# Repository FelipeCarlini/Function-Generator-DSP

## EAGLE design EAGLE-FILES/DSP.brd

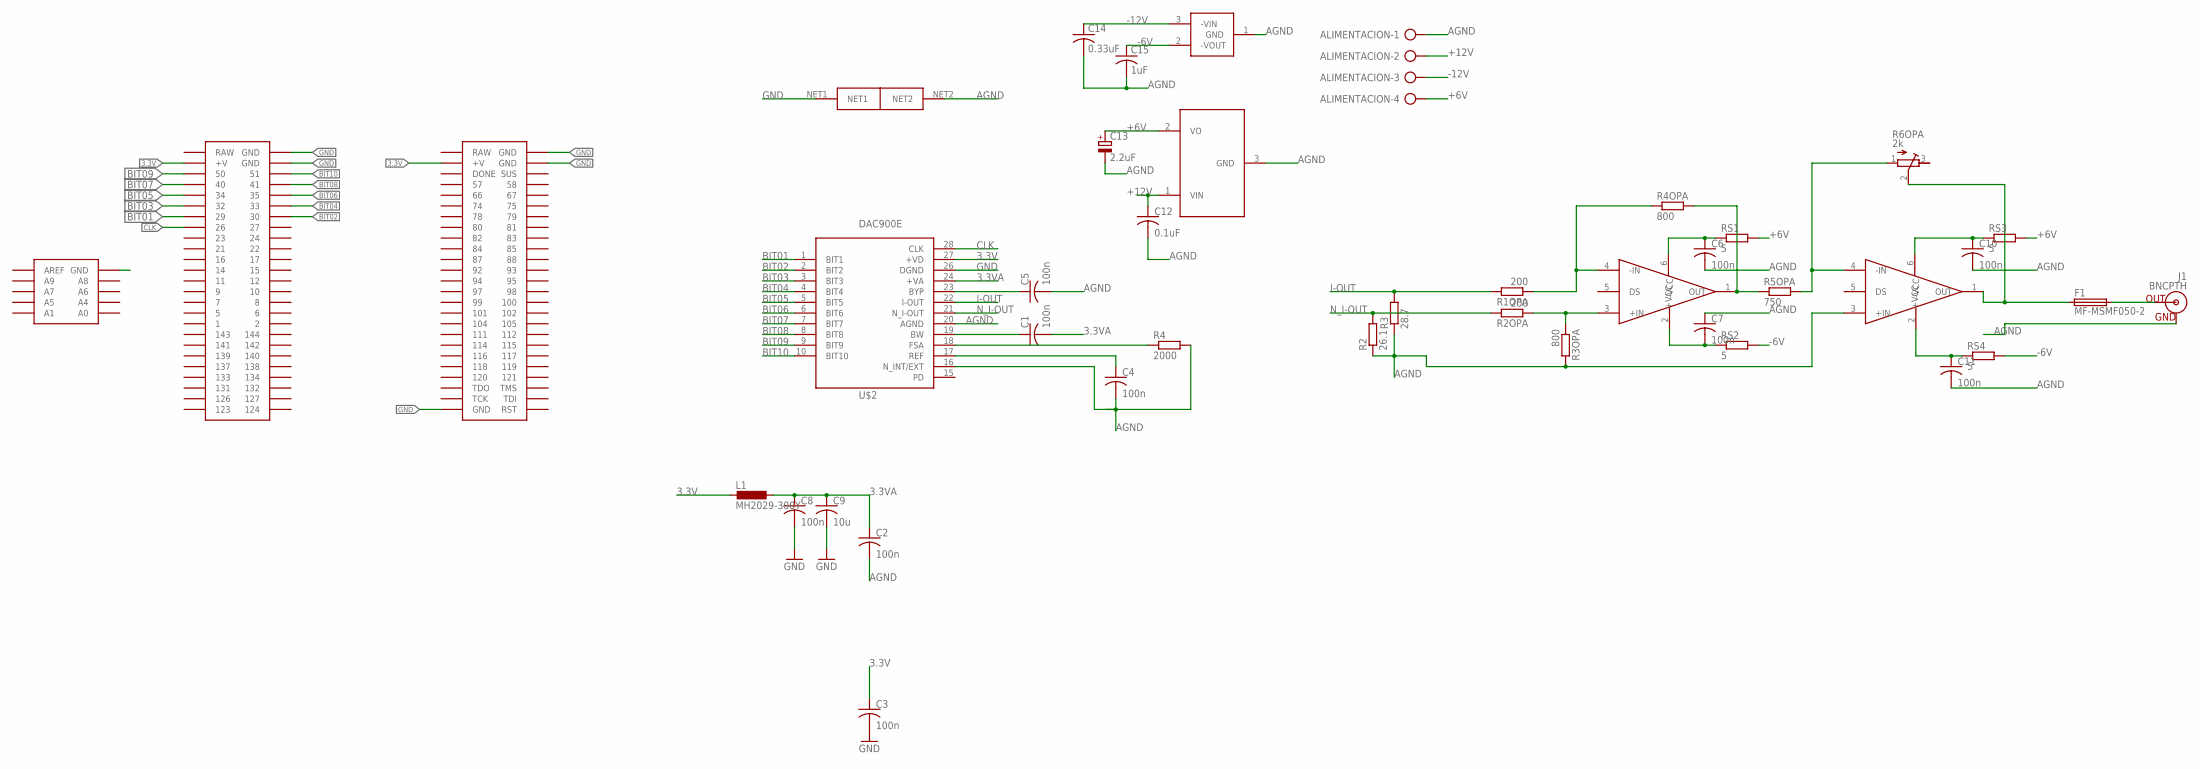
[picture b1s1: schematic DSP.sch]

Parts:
ALIMENTACION: AK300/4
C1, C2, C3, C4, C5, C6, C7, C8, C10, C11: 100n; C0603
C9: 10u; C0603
C12: 0.1uF; C0603
C13: 2.2uF; E2,5-6
C14: 0.33uF; C0603
C15: 1uF; C0603
F1: MF-MSMF050-2; 1812
J1: BNCPTH; BNC
L1: MH2029-300Y; R0805
R1OPA, R2OPA: 200; R0603
R2: 26.1; R0603
R3: 28.7; R0603
R3OPA, R4OPA: 800; R0603
R4: 2000; R0603
R5OPA: 750; R0603
R6OPA: 2k; RTRIM3296W
RS1, RS2, RS3, RS4: 5; 0309/10
U$1: MOJO_V2V3_NO_LABEL; MOJO_V3_NO_LABEL
U$2: DAC900E; TSSOP28
U$3, U$5: OPA683; SOT23-6
U$4: NET_TIE; NET-TIE
U$6: LF60; TO252
U$7: MC7906; TO263

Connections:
3.3V: C3.1, L1.2, U$1.V@1 (+V), U$1.V@2 (+V), U$2.27 (+VD)
3.3VA: C1.2, C2.1, C8.1, C9.1, L1.1, U$2.24 (+VA)
+6V: ALIMENTACION.4, C13.+, RS1.2, RS3.2, U$6.2 (VO)
+12V: ALIMENTACION.2, C12.1, U$6.1 (VIN)
-6V: C15.1, RS2.2, RS4.2, U$7.2 (-VOUT)
-12V: ALIMENTACION.3, C14.1, U$7.3 (-VIN)
AGND: ALIMENTACION.1, C2.2, C4.2, C5.2, C6.2, C7.1, C10.2, C11.2, C12.2, C13.-, C14.2, C15.2, J1.GND, R2.1, R3.1, R3OPA.2, R4.2, U$2.16 (N_INT/EXT), U$2.20 (AGND), U$4.NET2, U$5.3 (+IN), U$6.3 (GND), U$7.1 (GND)
BIT01: U$1.29, U$2.1 (BIT1)
BIT02: U$1.30, U$2.2 (BIT2)
BIT03: U$1.32, U$2.3 (BIT3)
BIT04: U$1.33, U$2.4 (BIT4)
BIT05: U$1.34, U$2.5 (BIT5)
BIT06: U$1.35, U$2.6 (BIT6)
BIT07: U$1.40, U$2.7 (BIT7)
BIT08: U$1.41, U$2.8 (BIT8)
BIT09: U$1.50, U$2.9 (BIT9)
BIT10: U$1.51, U$2.10 (BIT10)
CLK: U$1.26, U$2.28 (CLK)
GND: C3.2, C8.2, C9.2, U$1.GND@1 (GND), U$1.GND@2 (GND), U$1.GND@3 (GND), U$1.GND@4 (GND), U$1.GND@5 (GND), U$1.GND@6 (GND), U$2.26 (DGND), U$4.NET1
I-OUT: R1OPA.2, R3.2, U$2.22 (I-OUT)
unnamed: R5OPA.2, R6OPA.1 (A), U$5.4 (-IN)
unnamed: F1.1, R6OPA.2 (S), U$5.1 (OUT)
unnamed: R2OPA.1, R3OPA.1, U$3.3 (+IN)
unnamed: R1OPA.1, R4OPA.1, U$3.4 (-IN)
unnamed: R4OPA.2, R5OPA.1, U$3.1 (OUT)
unnamed: C10.1, RS3.1, U$5.6 (+VCC)
unnamed: C11.1, RS4.1, U$5.2 (-VCC)
unnamed: C6.1, RS1.1, U$3.6 (+VCC)
unnamed: C7.2, RS2.1, U$3.2 (-VCC)
unnamed: F1.2, J1.S (OUT)
unnamed: C5.1, U$2.23 (BYP)
unnamed: C1.1, U$2.19 (BW)
unnamed: R4.1, U$2.18 (FSA)
unnamed: C4.1, U$2.17 (REF)
N_I-OUT: R2.2, R2OPA.2, U$2.21 (N_I-OUT)

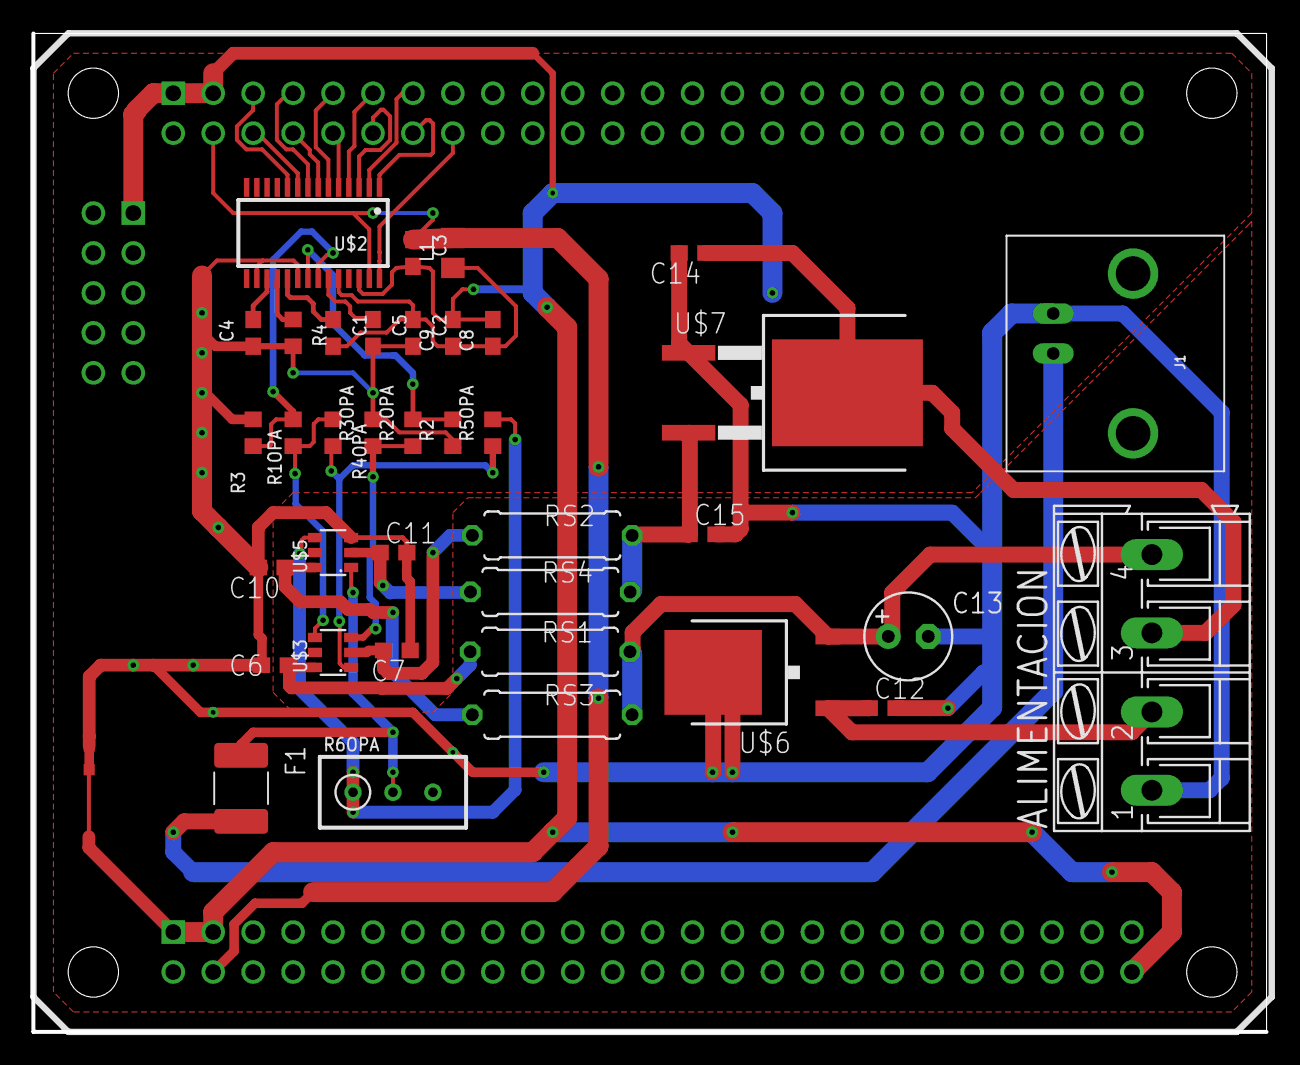
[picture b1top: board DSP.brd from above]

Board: 2 copper layers, 78.4 x 63.5 mm, 39 parts (0 on the bottom side), 35 nets.

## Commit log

2020-08-21 [ADD] gitignore
2020-08-22 [ADD] VHDL Files
2020-08-22 [ADD] ucf file
2020-08-22 [ADD] esp files
2020-09-11 [ADD] User interface
2020-09-11 [ADD] reactive chart
2020-09-12 [ADD] minor change label for radio input
2020-09-13 minor changes
2020-09-13 [ADD] images folder
2020-09-24 [ADD] eagle files

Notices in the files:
parts and their libraries:
SparkFun-Connectors: Licensing: Creative Commons ShareAlike 4.0 International - https://creativecommons.org/licenses/by-sa/4.0
